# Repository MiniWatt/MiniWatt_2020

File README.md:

# BMS-Adapter
Evolution de la carte BMS-Adapter, pour passage de la batterie 38V (10S) à 48V (12S)
Initialisation

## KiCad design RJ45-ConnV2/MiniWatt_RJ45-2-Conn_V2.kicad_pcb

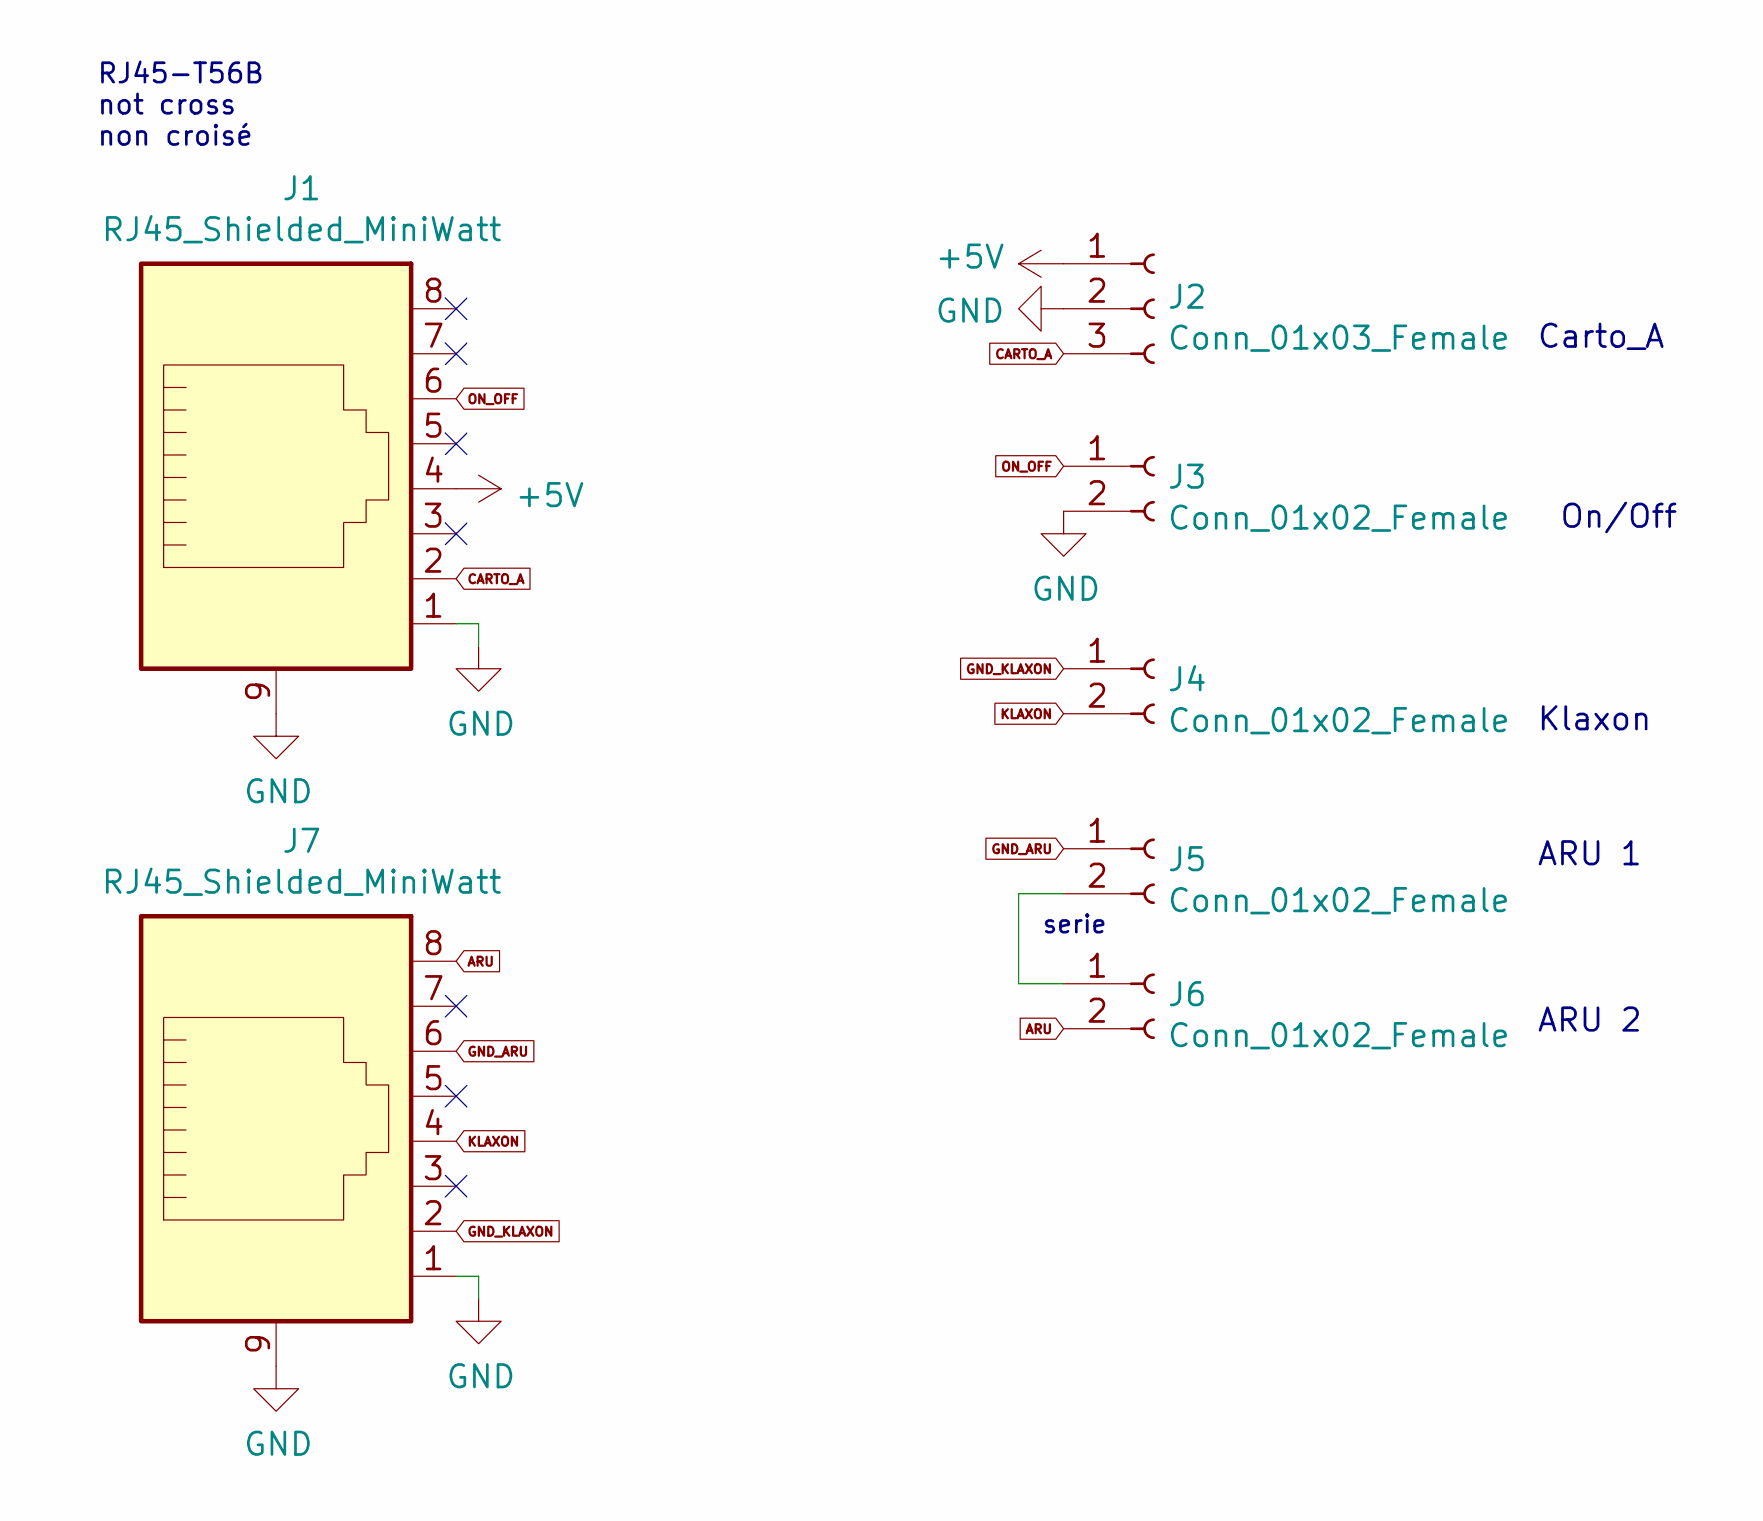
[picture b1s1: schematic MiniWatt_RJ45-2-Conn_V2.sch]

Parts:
J1, J7: RJ45_Shielded_MiniWatt; RJ45_CAN
J2: Conn_01x03_Female; Molex_Micro-Fit_3.0_43650-0315_1x03_P3.00mm_Vertical
J3, J4, J5, J6: Conn_01x02_Female; Molex_Micro-Fit_3.0_43650-0215_1x02_P3.00mm_Vertical

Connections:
+5V: J1.4, J2.1
ARU: J6.2, J7.8
CARTO_A: J1.2, J2.3
GND: J1.1, J1.9, J2.2, J3.2, J7.1, J7.9
GND_ARU: J5.1, J7.6
GND_KLAXON: J4.1, J7.2
KLAXON: J4.2, J7.4
unnamed: J5.2, J6.1
ON_OFF: J1.6, J3.1

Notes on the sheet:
ARU 1
ARU 2
Klaxon
serie
On/Off
Carto_A
RJ45-T56B not cross non croisé

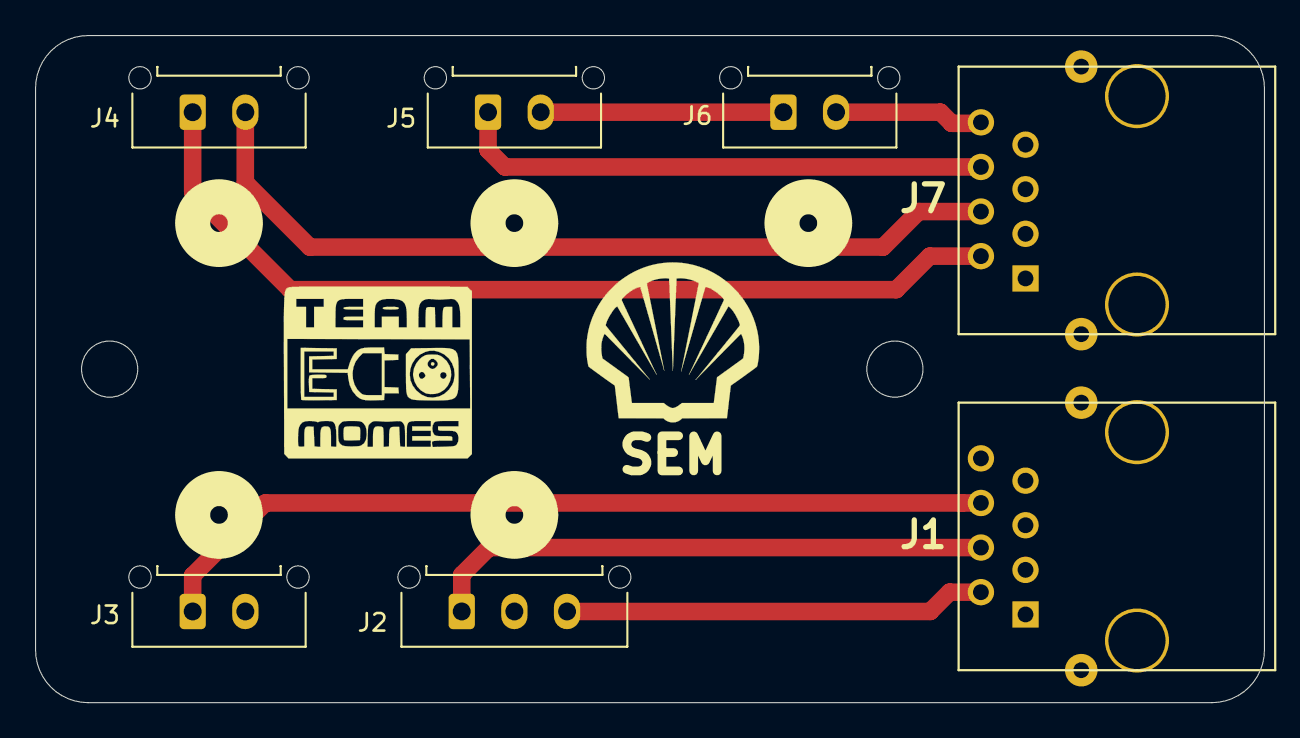
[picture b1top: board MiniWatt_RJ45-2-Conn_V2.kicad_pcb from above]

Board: 2 copper layers, 70.0 x 38.0 mm, 7 parts (0 on the bottom side), 9 nets.

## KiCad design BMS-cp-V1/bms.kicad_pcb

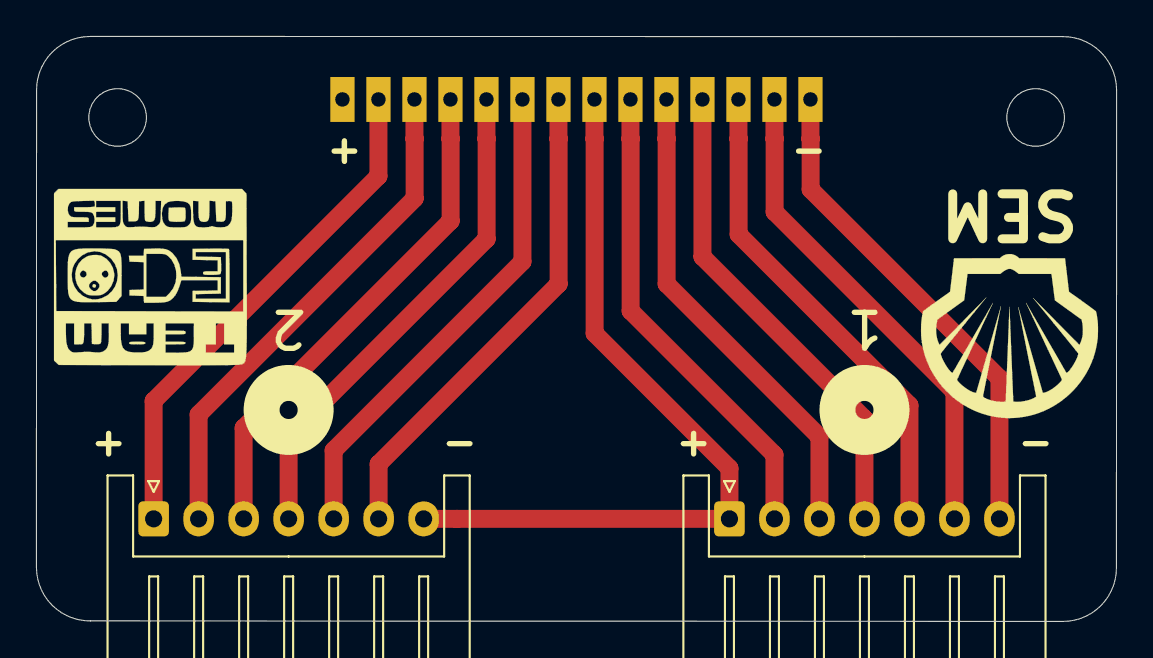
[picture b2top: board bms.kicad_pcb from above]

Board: 2 copper layers, 60.0 x 32.5 mm, 3 parts (1 on the bottom side), 13 nets.

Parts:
-1+1, -2+1: Conn_01x07; JST_XH_S7B-XH-A_1x07_P2.50mm_Horizontal
BMS: Conn_01x14; PinHeader_1x14_P2.00mm_Vertical

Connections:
unnamed: -1+1.1, -2+1.7, BMS.7
unnamed: -1+1.2, BMS.6
unnamed: -1+1.3, BMS.5
unnamed: -1+1.4, BMS.4
unnamed: -1+1.5, BMS.3
unnamed: -1+1.6, BMS.2
unnamed: -1+1.7, BMS.1
unnamed: -2+1.1, BMS.13
unnamed: -2+1.2, BMS.12
unnamed: -2+1.3, BMS.11
unnamed: -2+1.4, BMS.10
unnamed: -2+1.5, BMS.9
unnamed: -2+1.6, BMS.8

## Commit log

2020-02-16 Evolution dela carte BBMS adapter, pour un passage de batteries Lipo 10 cellules à 12 cellules
2020-02-16 Initialisation du projet
    Mise à disposition des fichiers
2020-02-18 Mise à jour prennant en compte les nouvelles cotes définies par Nicolas, le 17/02/2020.
2020-02-18 Ajout du fichier STEP pour FreeCAD
2020-02-29 Issue : Nouvelle version de la carte RJ15 Qui : Christophe Quoi : - connecteur : connecteur Molex micro-fit 3 - renumérotation des connecteur pour meilleur lecture - ajout pastilles blanche de 5mm de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
